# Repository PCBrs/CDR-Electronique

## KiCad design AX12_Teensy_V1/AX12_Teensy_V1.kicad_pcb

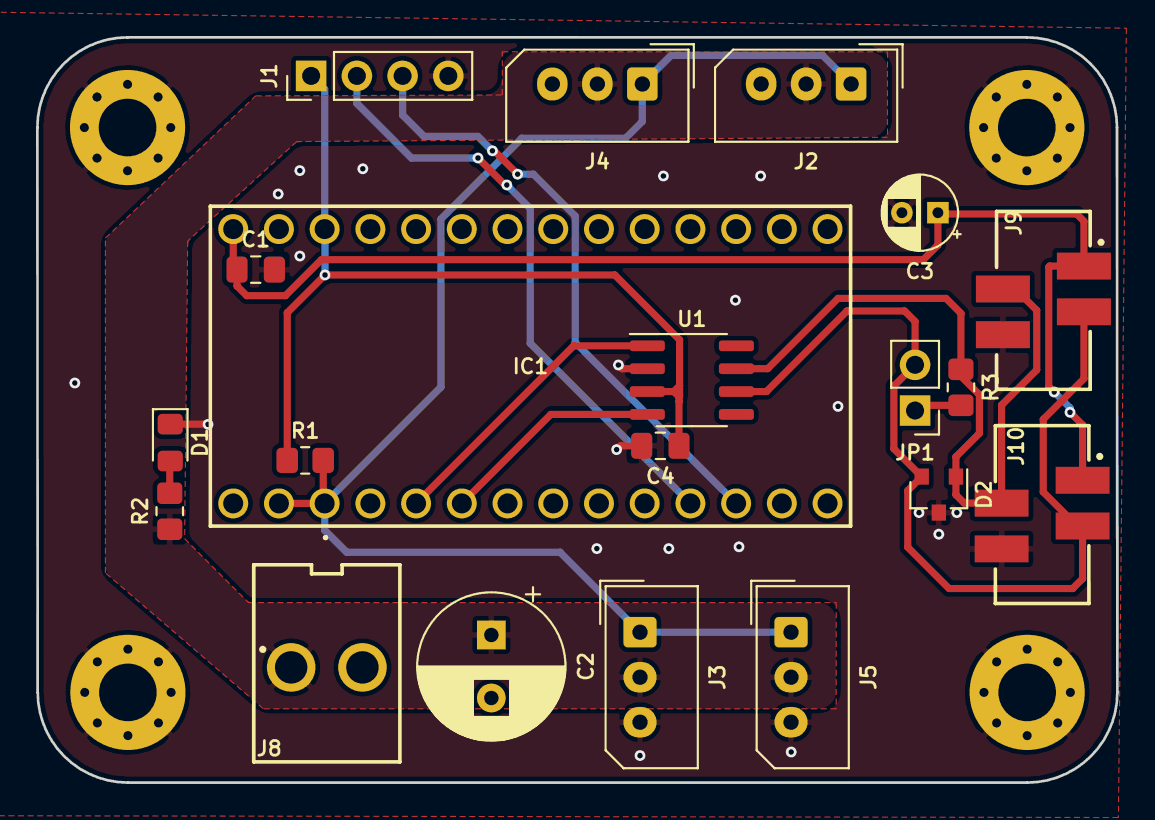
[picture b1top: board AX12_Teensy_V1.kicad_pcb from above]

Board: 2 copper layers, 60.0 x 41.4 mm, 24 parts (0 on the bottom side), 13 nets.

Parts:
C1, C4: 100n; C_0805_2012Metric_Pad1.18x1.45mm_HandSolder
C2: 100u; CP_Radial_D8.0mm_P3.50mm
C3: 10u; CP_Radial_D4.0mm_P2.00mm
D1: LED_12V; LED_0805_2012Metric_Pad1.15x1.40mm_HandSolder
D2: TVS; SOT-23
H1, H2, H3, H4: MountingHole_Pad; MountingHole_3.2mm_M3_Pad_Via
IC1: TEENSY3.2; TEENSY32
J1: uart; PinHeader_1x04_P2.54mm_Vertical
J2, J3, J4, J5: AX12; Molex_SPOX_5267-03A_1x03_P2.50mm_Vertical
J8: 12VP; Wuerth_3.96mm_2pin_645002114822
J9, J10: Conn_CAN; 690367290476
JP1: 120; PinHeader_1x02_P2.54mm_Vertical
R1: 1.5K; R_0805_2012Metric_Pad1.20x1.40mm_HandSolder
R2: 2k; R_0805_2012Metric_Pad1.20x1.40mm_HandSolder
R3: 120; R_0805_2012Metric_Pad1.20x1.40mm_HandSolder
U1: SN65HVD232; SOIC-8_3.9x4.9mm_P1.27mm

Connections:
+3V3: C4.1, IC1.24, J1.1, R1.1, U1.3
+5V: C1.1, C3.1, IC1.26, J9.1, J10.1
+12V: C2.1, J2.2, J3.2, J4.2, J5.2, J8.1, R2.1
/AX12_BUS: IC1.1, IC1.37, J2.1, J3.1, J4.1, J5.1, R1.2
/CANH: D2.1, J9.2, J10.2, R3.1, U1.7
/CANL: D2.2, J9.3, J10.3, JP1.2, U1.6
/CANRX: IC1.4, U1.4
/CANTX: IC1.3, U1.1
/RX: IC1.10, J1.3
/TX: IC1.9, J1.2
GND: C1.2, C2.2, C3.2, C4.2, D1.1, D2.3, H1.1, H2.1, H3.1, H4.1, J1.4, J2.3, J3.3, J4.3, J5.3, J8.2, J9.4, J10.4, U1.2
unnamed: D1.2, R2.2
unnamed: JP1.1, R3.2

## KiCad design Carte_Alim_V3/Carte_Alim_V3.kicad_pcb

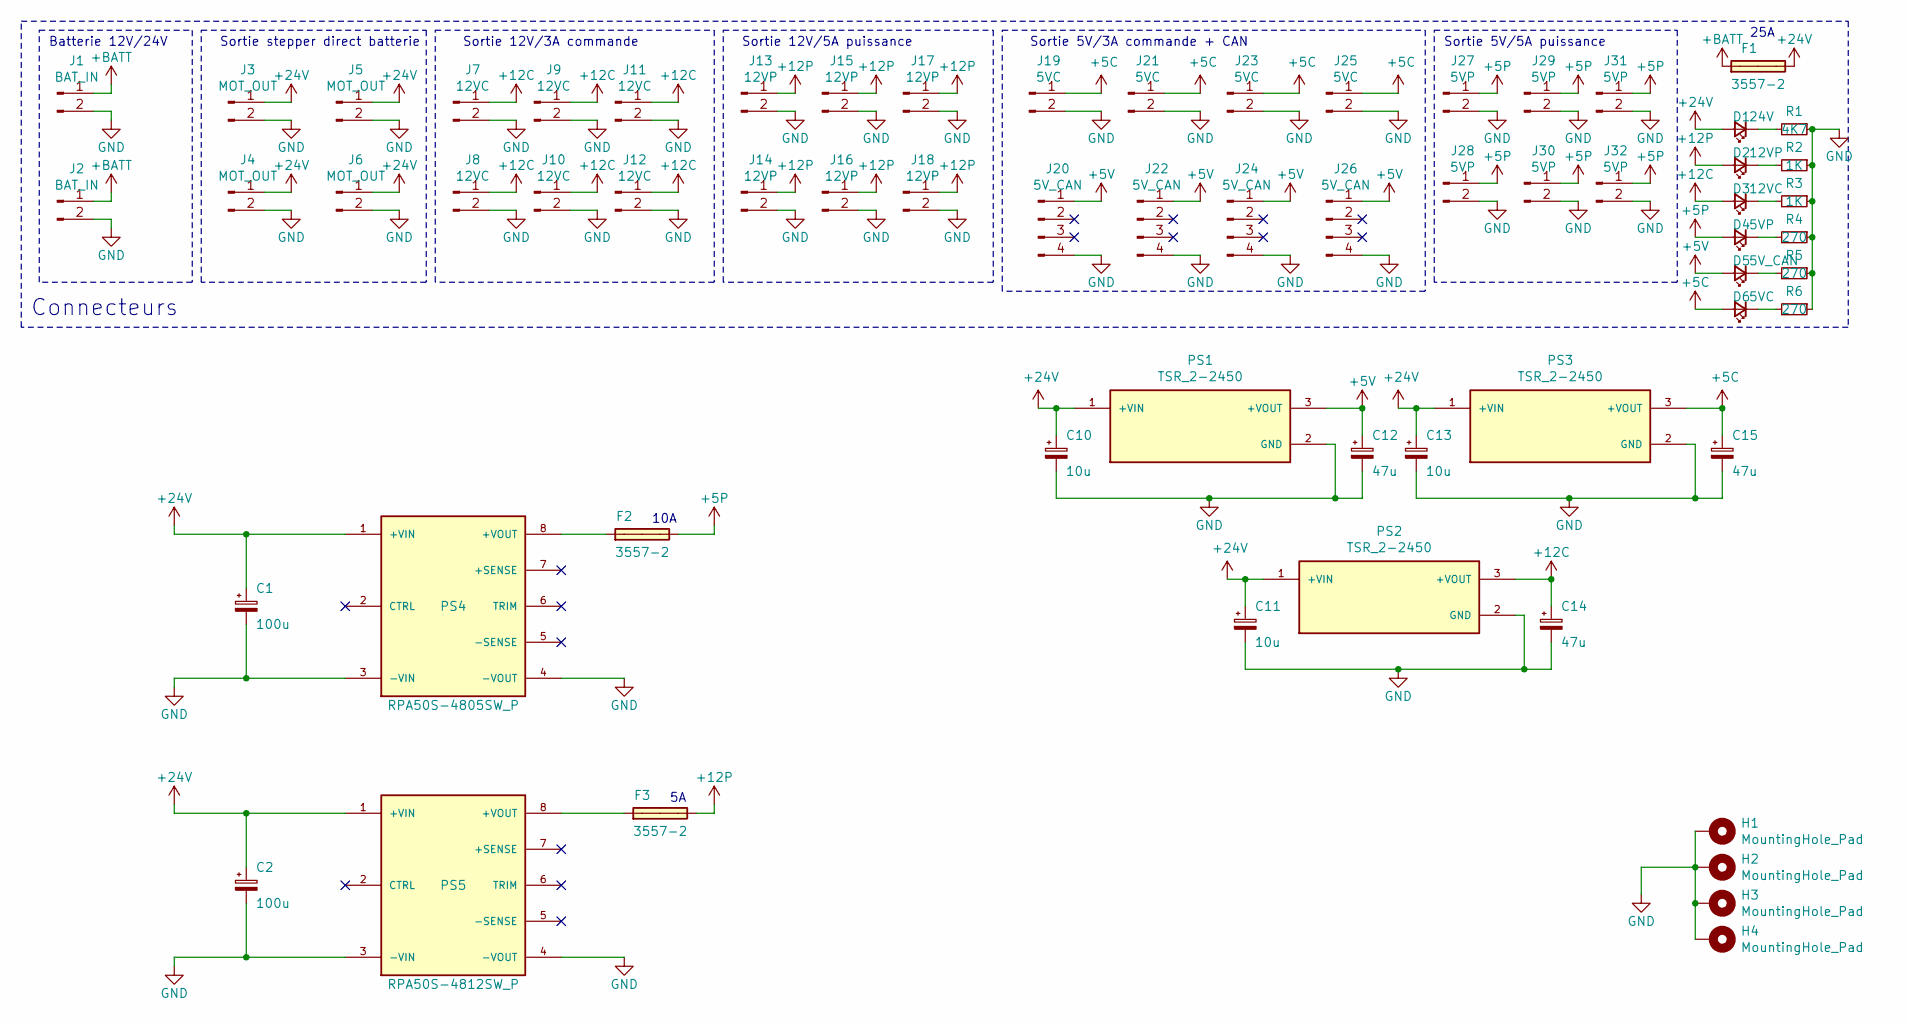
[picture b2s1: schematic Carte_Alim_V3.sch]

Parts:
C1, C2: 100u; CP_Radial_D8.0mm_P3.50mm
C10, C11, C13: 10u; CP_Radial_D4.0mm_P2.00mm
C12, C14, C15: 47u; CP_Radial_D4.0mm_P2.00mm
D1: 24V; LED_0805_2012Metric_Pad1.15x1.40mm_HandSolder
D2: 12VP; LED_0805_2012Metric_Pad1.15x1.40mm_HandSolder
D3: 12VC; LED_0805_2012Metric_Pad1.15x1.40mm_HandSolder
D4: 5VP; LED_0805_2012Metric_Pad1.15x1.40mm_HandSolder
D5: 5V_CAN; LED_0805_2012Metric_Pad1.15x1.40mm_HandSolder
D6: 5VC; LED_0805_2012Metric_Pad1.15x1.40mm_HandSolder
F1, F2, F3: 3557-2; FUSE_3557-2
H1, H2, H3, H4: MountingHole_Pad; MountingHole_3.2mm_M3_Pad_Via
J1, J2: BAT_IN; Wuerth_batcon_691313710002
J3, J4, J5, J6: MOT_OUT; Wuerth_batcon_691313710002
J7, J8, J9, J10, J11, J12: 12VC; Wuerth_2.54mm_2pins_61900211121
J13, J14, J15, J16, J17, J18: 12VP; Wuerth_3.96mm_2pin_645002114822
J19, J21, J23, J25: 5VC; Wuerth_2.54mm_2pins_61900211121
J20, J22, J24, J26: 5V_CAN; Wuerth_2mm_4pin_62000411622
J27, J28, J29, J30, J31, J32: 5VP; Wuerth_3.96mm_2pin_645002114822
PS1, PS2, PS3: TSR_2-2450; CONV_TSR_2-2450; PARTREV May 14, 2020
PS4: RPA50S-4805SW_P; RPA50S-4805SWP; PARTREV 3/2020
PS5: RPA50S-4812SW_P; RPA50S-4812SW; PARTREV 1
R1: 4K7; R_0805_2012Metric_Pad1.20x1.40mm_HandSolder
R2, R3: 1K; R_0805_2012Metric_Pad1.20x1.40mm_HandSolder
R4, R5, R6: 270; R_0805_2012Metric_Pad1.20x1.40mm_HandSolder

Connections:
+5C: C15.1, D6.2 (A), J19.1, J21.1, J23.1, J25.1, PS3.3 (+VOUT)
+5P: D4.2 (A), F2.3, J27.1, J28.1, J29.1, J30.1, J31.1, J32.1
+5V: C12.1, D5.2 (A), J20.1, J22.1, J24.1, J26.1, PS1.3 (+VOUT)
+12C: C14.1, D3.2 (A), J7.1, J8.1, J9.1, J10.1, J11.1, J12.1, PS2.3 (+VOUT)
+12P: D2.2 (A), F3.3, J13.1, J14.1, J15.1, J16.1, J17.1, J18.1
+24V: C1.1, C2.1, C10.1, C11.1, C13.1, D1.2 (A), F1.3, J3.1, J4.1, J5.1, J6.1, PS1.1 (+VIN), PS2.1 (+VIN), PS3.1 (+VIN), PS4.1 (+VIN), PS5.1 (+VIN)
+BATT: F1.1, J1.1, J2.1
GND: C1.2, C2.2, C10.2, C11.2, C12.2, C13.2, C14.2, C15.2, H1.1, H2.1, H3.1, H4.1, J1.2, J2.2, J3.2, J4.2, J5.2, J6.2, J7.2, J8.2, J9.2, J10.2, J11.2, J12.2, J13.2, J14.2, J15.2, J16.2, J17.2, J18.2, J19.2, J20.4, J21.2, J22.4, J23.2, J24.4, J25.2, J26.4, J27.2, J28.2, J29.2, J30.2, J31.2, J32.2, PS1.2 (GND), PS2.2 (GND), PS3.2 (GND), PS4.3 (-VIN), PS4.4 (-VOUT), PS5.3 (-VIN), PS5.4 (-VOUT), R1.1, R2.1, R3.1, R4.1, R5.1, R6.1
unnamed: D1.1 (K), R1.2
unnamed: D2.1 (K), R2.2
unnamed: D3.1 (K), R3.2
unnamed: D4.1 (K), R4.2
unnamed: D5.1 (K), R5.2
unnamed: D6.1 (K), R6.2
unnamed: F2.1, PS4.8 (+VOUT)
unnamed: F3.1, PS5.8 (+VOUT)

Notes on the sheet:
Connecteurs
Batterie 12V/24V
Sortie stepper direct batterie
Sortie 12V/3A commande
Sortie 12V/5A puissance
Sortie 5V/3A commande + CAN
Sortie 5V/5A puissance
10A
25A

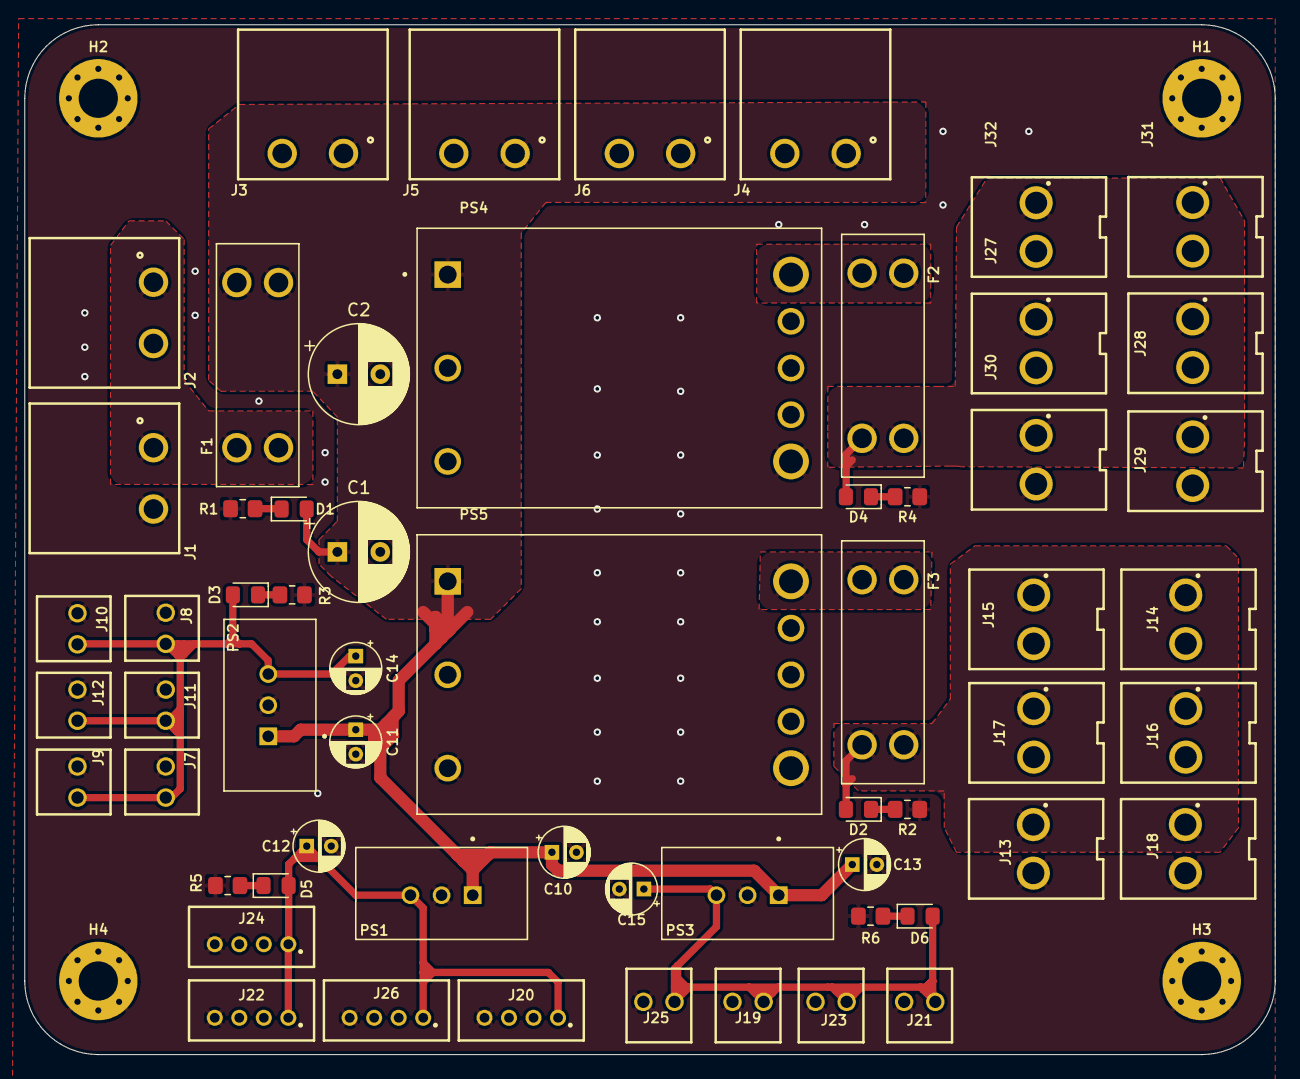
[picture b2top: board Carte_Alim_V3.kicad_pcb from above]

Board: 2 copper layers, 102.0 x 84.0 mm, 64 parts (0 on the bottom side), 16 nets.

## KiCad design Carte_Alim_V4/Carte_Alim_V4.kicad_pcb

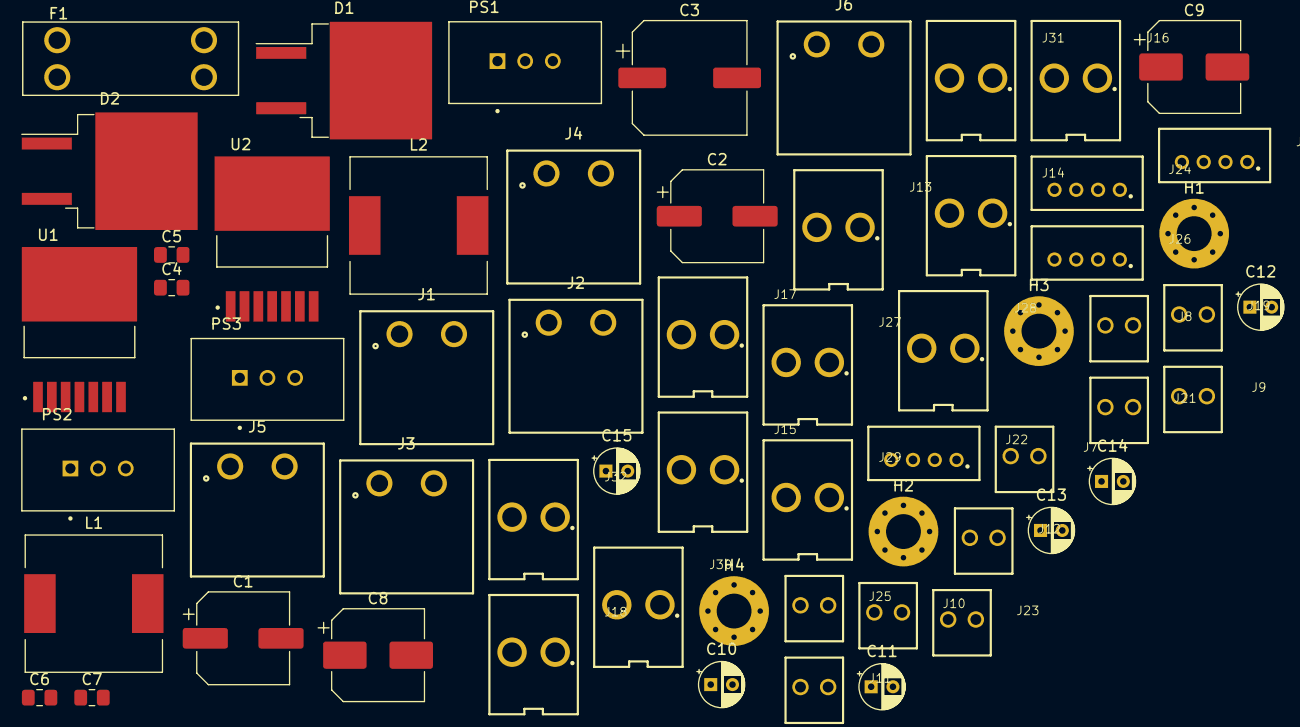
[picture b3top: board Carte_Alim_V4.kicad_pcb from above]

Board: 2 copper layers, 61 parts (0 on the bottom side), 13 nets, no tracks yet.

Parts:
C1, C2: 82u; CP_Elec_8x6.9
C3: 330u; CP_Elec_10x12.6
C4, C5: 100n; C_0805_2012Metric_Pad1.18x1.45mm_HandSolder
C6, C7: 10n; C_0805_2012Metric_Pad1.18x1.45mm_HandSolder
C8, C9: 330u; CP_Elec_8x6.2
C10, C11, C13: 10u; CP_Radial_D4.0mm_P2.00mm
C12, C14, C15: 47u; CP_Radial_D4.0mm_P2.00mm
D1, D2: VB20100S-E3/8W; TO-263-2_TabPin1
F1: 3557-2; FUSE_3557-2
H1, H2, H3, H4: MountingHole_Pad; MountingHole_3.2mm_M3_Pad_Via
J1, J2: BAT_IN; Wuerth_batcon_691313710002
J3, J4, J5, J6: MOT_OUT; Wuerth_batcon_691313710002
J7, J8, J9, J10, J11, J12: 12VC; Wuerth_2.54mm_2pins_61900211121
J13, J14, J15, J16, J17, J18: 12VP; Wuerth_3.96mm_2pin_645002114822
J19, J21, J23, J25: 5VC; Wuerth_2.54mm_2pins_61900211121
J20, J22, J24, J26: 5V_CAN; Wuerth_2mm_4pin_62000411622
J27, J28, J29, J30, J31, J32: 5VP; Wuerth_3.96mm_2pin_645002114822
L1, L2: MSS1210-153MED; L_12x12mm_H8mm
PS1, PS2, PS3: TSR_2-2450; CONV_TSR_2-2450
U1: LM2678S-5.0; TO127P1435X464-8N
U2: LM2678S-12; TO127P1435X464-8N

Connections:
+5C: C15.1, J19.1, J21.1, J23.1, J25.1, PS3.3
+5P: C8.1, J27.1, J28.1, J29.1, J30.1, J31.1, J32.1, L1.2, U1.6
+5V: C12.1, J20.1, J22.1, J24.1, J26.1, PS1.3
+12C: C14.1, J7.1, J8.1, J9.1, J10.1, J11.1, J12.1, PS2.3
+12P: C9.1, J13.1, J14.1, J15.1, J16.1, J17.1, J18.1, L2.2, U2.6
+24V: C1.1, C2.1, C3.1, C4.1, C5.1, C10.1, C11.1, C13.1, F1.3, PS1.1, PS2.1, PS3.1, U1.2, U2.2
+BATT: F1.1, J1.1, J2.1, J3.1, J4.1, J5.1, J6.1
GND: C1.2, C2.2, C4.2, C8.2, C10.2, C11.2, C12.2, C13.2, C14.2, C15.2, D1.2, H1.1, H2.1, H3.1, H4.1, J1.2, J2.2, J3.2, J4.2, J5.2, J6.2, J7.2, J8.2, J9.2, J10.2, J11.2, J12.2, J13.2, J14.2, J15.2, J16.2, J17.2, J18.2, J19.2, J20.4, J21.2, J22.4, J23.2, J24.4, J25.2, J26.4, J27.2, J28.2, J29.2, J30.2, J31.2, J32.2, PS1.2, PS2.2, PS3.2, U1.4, U1.8
unnamed: C3.2, C5.2, C9.2, D2.2, U2.4, U2.8
unnamed: C6.1, U1.3
unnamed: C6.2, D1.1, L1.1, U1.1
unnamed: C7.1, U2.3
unnamed: C7.2, D2.1, L2.1, U2.1

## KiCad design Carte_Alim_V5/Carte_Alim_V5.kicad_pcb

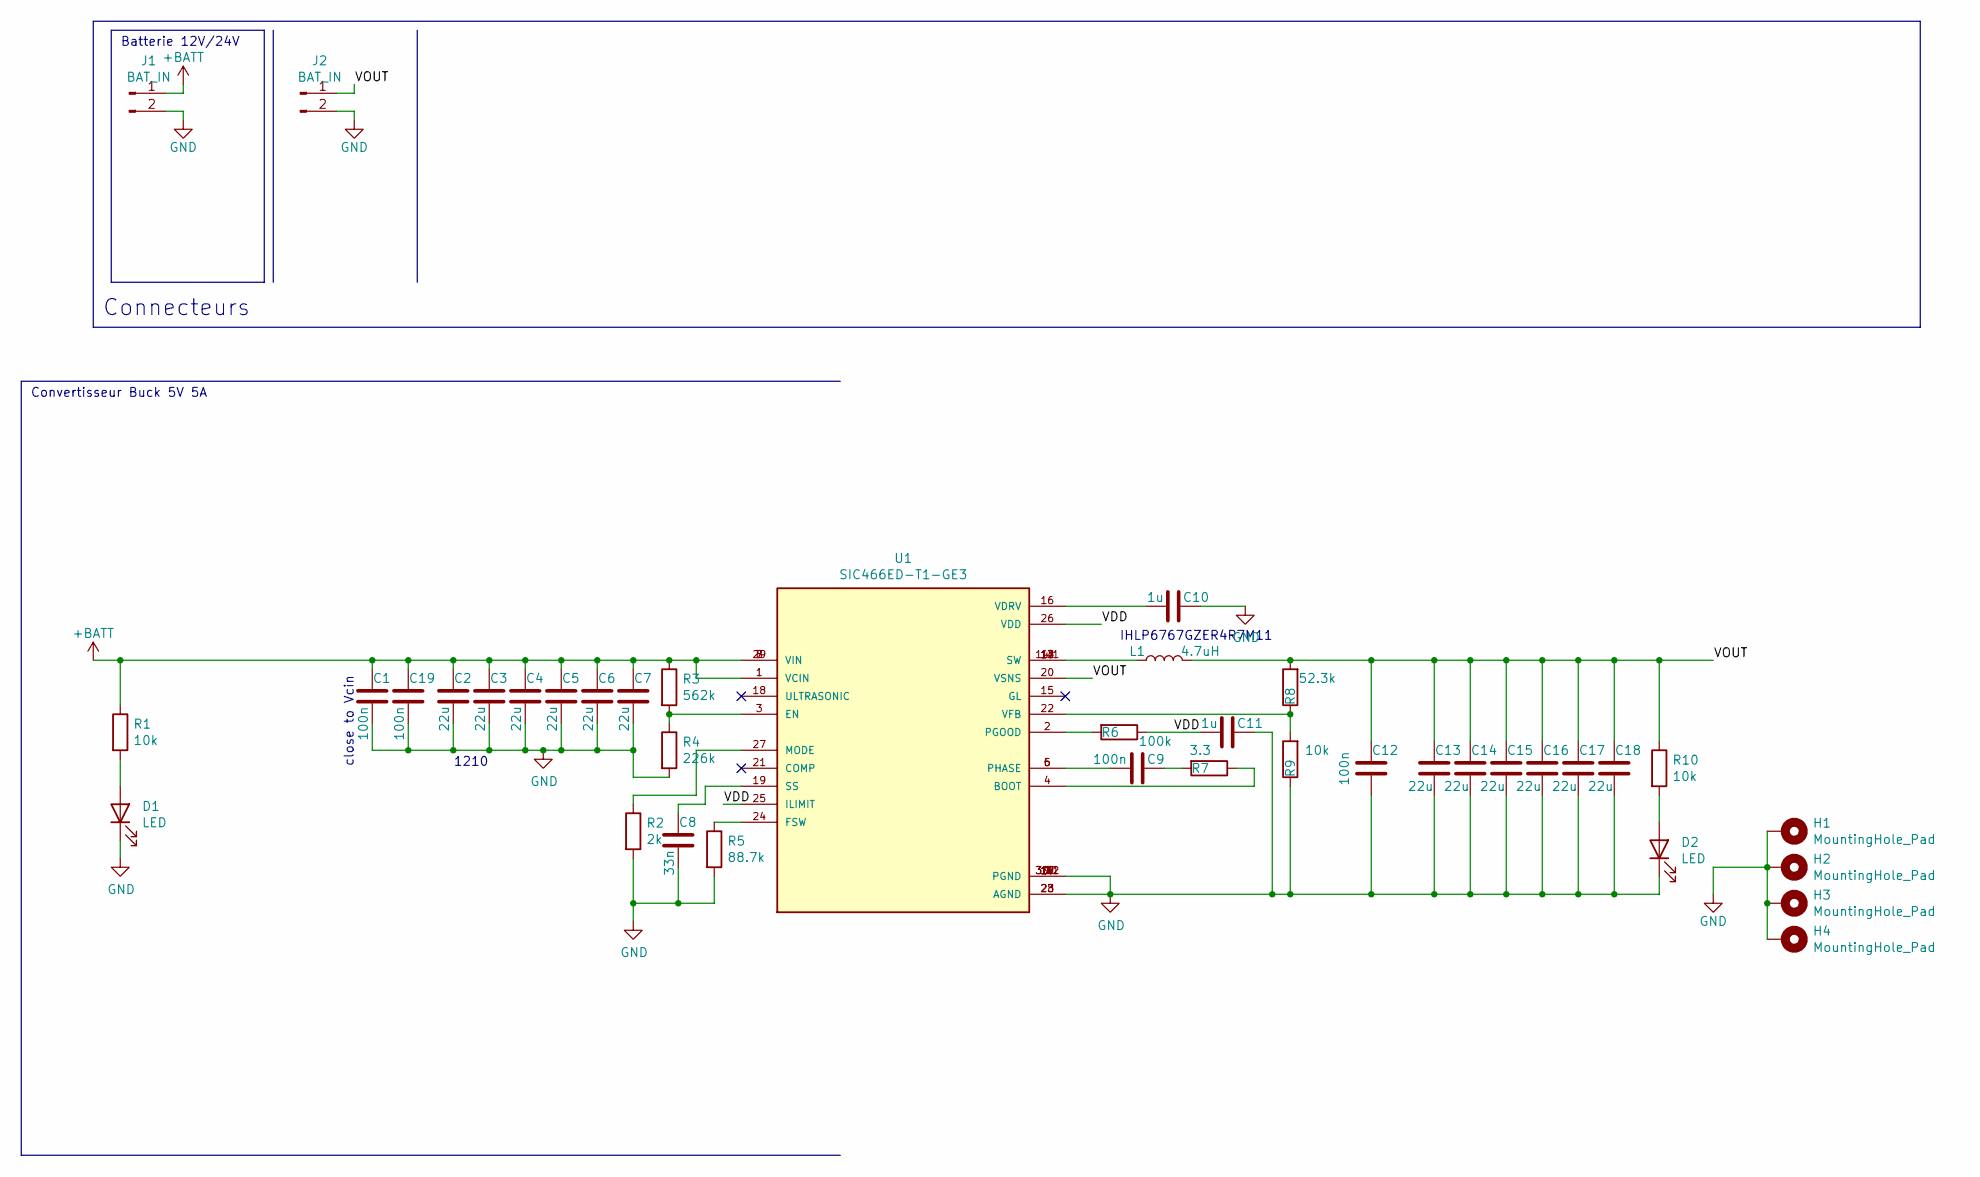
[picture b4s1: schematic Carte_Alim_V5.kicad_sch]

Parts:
C1, C9, C12, C19: 100n; C_0805_2012Metric_Pad1.15x1.40mm_HandSolder
C2, C3, C4, C5, C6, C7, C13, C14, C15, C16, C17, C18: 22u; C_1210_3225Metric_Pad1.42x2.65mm_HandSolder
C8: 33n; C_0805_2012Metric_Pad1.15x1.40mm_HandSolder
C10, C11: 1u; C_0805_2012Metric_Pad1.15x1.40mm_HandSolder
D1, D2: LED; LED_0805_2012Metric_Pad1.15x1.40mm_HandSolder
H1, H2, H3, H4: MountingHole_Pad; MountingHole_3.2mm_M3_Pad_Via
J1, J2: BAT_IN; PhoenixContact_MSTBVA_2,5_2-G-5,08_1x02_P5.08mm_Vertical
L1: 4.7uH; L_Vishay_IHLP-6767
R1, R9: 10k; R_0603_1608Metric_Pad1.05x0.95mm_HandSolder
R2: 2k; R_0603_1608Metric_Pad1.05x0.95mm_HandSolder
R3: 562k; R_0603_1608Metric_Pad1.05x0.95mm_HandSolder
R4: 226k; R_0603_1608Metric_Pad1.05x0.95mm_HandSolder
R5: 88.7k; R_0603_1608Metric_Pad1.05x0.95mm_HandSolder
R6: 100k; R_0603_1608Metric_Pad1.05x0.95mm_HandSolder
R7: 3.3; R_0603_1608Metric_Pad1.05x0.95mm_HandSolder
R8: 52.3k; R_0603_1608Metric_Pad1.05x0.95mm_HandSolder
R10: 10k; R_0603_1608Metric_Pad0.98x0.95mm_HandSolder
U1: SIC466ED-T1-GE3; CONV_SIC461ED-T1-GE3; PARTREV M

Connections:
+BATT: C1.1, C2.1, C3.1, C4.1, C5.1, C6.1, C7.1, C19.1, J1.1, R1.1, R3.1, U1.1 (VCIN), U1.7 (VIN), U1.8 (VIN), U1.29 (VIN)
/VDD: C11.2, R6.1, U1.25 (ILIMIT), U1.26 (VDD)
/VOUT: C12.1, C13.1, C14.1, C15.1, C16.1, C17.1, C18.1, J2.1, L1.2, R8.2, R10.1, U1.20 (VSNS)
GND: C1.2, C2.2, C3.2, C4.2, C5.2, C6.2, C7.2, C8.2, C10.1, C11.1, C12.2, C13.2, C14.2, C15.2, C16.2, C17.2, C18.2, C19.2, D1.1 (K), D2.1 (K), H1.1, H2.1, H3.1, H4.1, J1.2, J2.2, R2.2, R4.2, R5.2, R9.1, U1.9 (PGND), U1.10 (PGND), U1.11 (PGND), U1.17 (PGND), U1.23 (AGND), U1.28 (AGND), U1.30.1 (PGND), U1.30.2 (PGND)
unnamed: C8.1, U1.19 (SS)
unnamed: C9.1, R7.2
unnamed: C9.2, U1.5 (PHASE), U1.6 (PHASE)
unnamed: C10.2, U1.16 (VDRV)
unnamed: D1.2 (A), R1.2
unnamed: D2.2 (A), R10.2
unnamed: L1.1, U1.12 (SW), U1.13 (SW), U1.14 (SW), U1.14.1 (SW)
unnamed: R2.1, U1.27 (MODE)
unnamed: R3.2, R4.1, U1.3 (EN)
unnamed: R5.1, U1.24 (FSW)
unnamed: R6.2, U1.2 (PGOOD)
unnamed: R7.1, U1.4 (BOOT)
unnamed: R8.1, R9.2, U1.22 (VFB)

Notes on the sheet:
Convertisseur Buck 5V 5A
1210
close to Vcin
Connecteurs
IHLP6767GZER4R7M11
Batterie 12V/24V

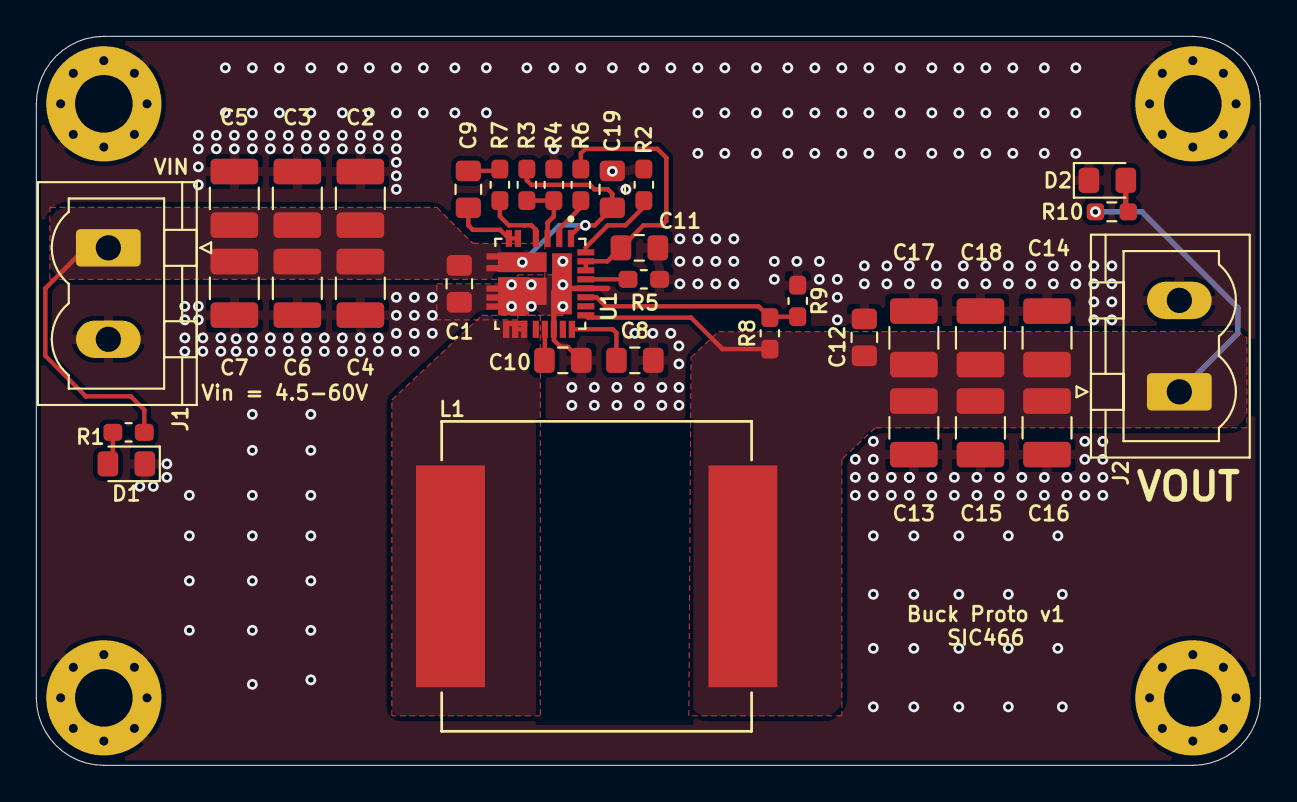
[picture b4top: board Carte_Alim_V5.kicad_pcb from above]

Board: 2 copper layers, 68.0 x 40.5 mm, 39 parts (0 on the bottom side), 17 nets.

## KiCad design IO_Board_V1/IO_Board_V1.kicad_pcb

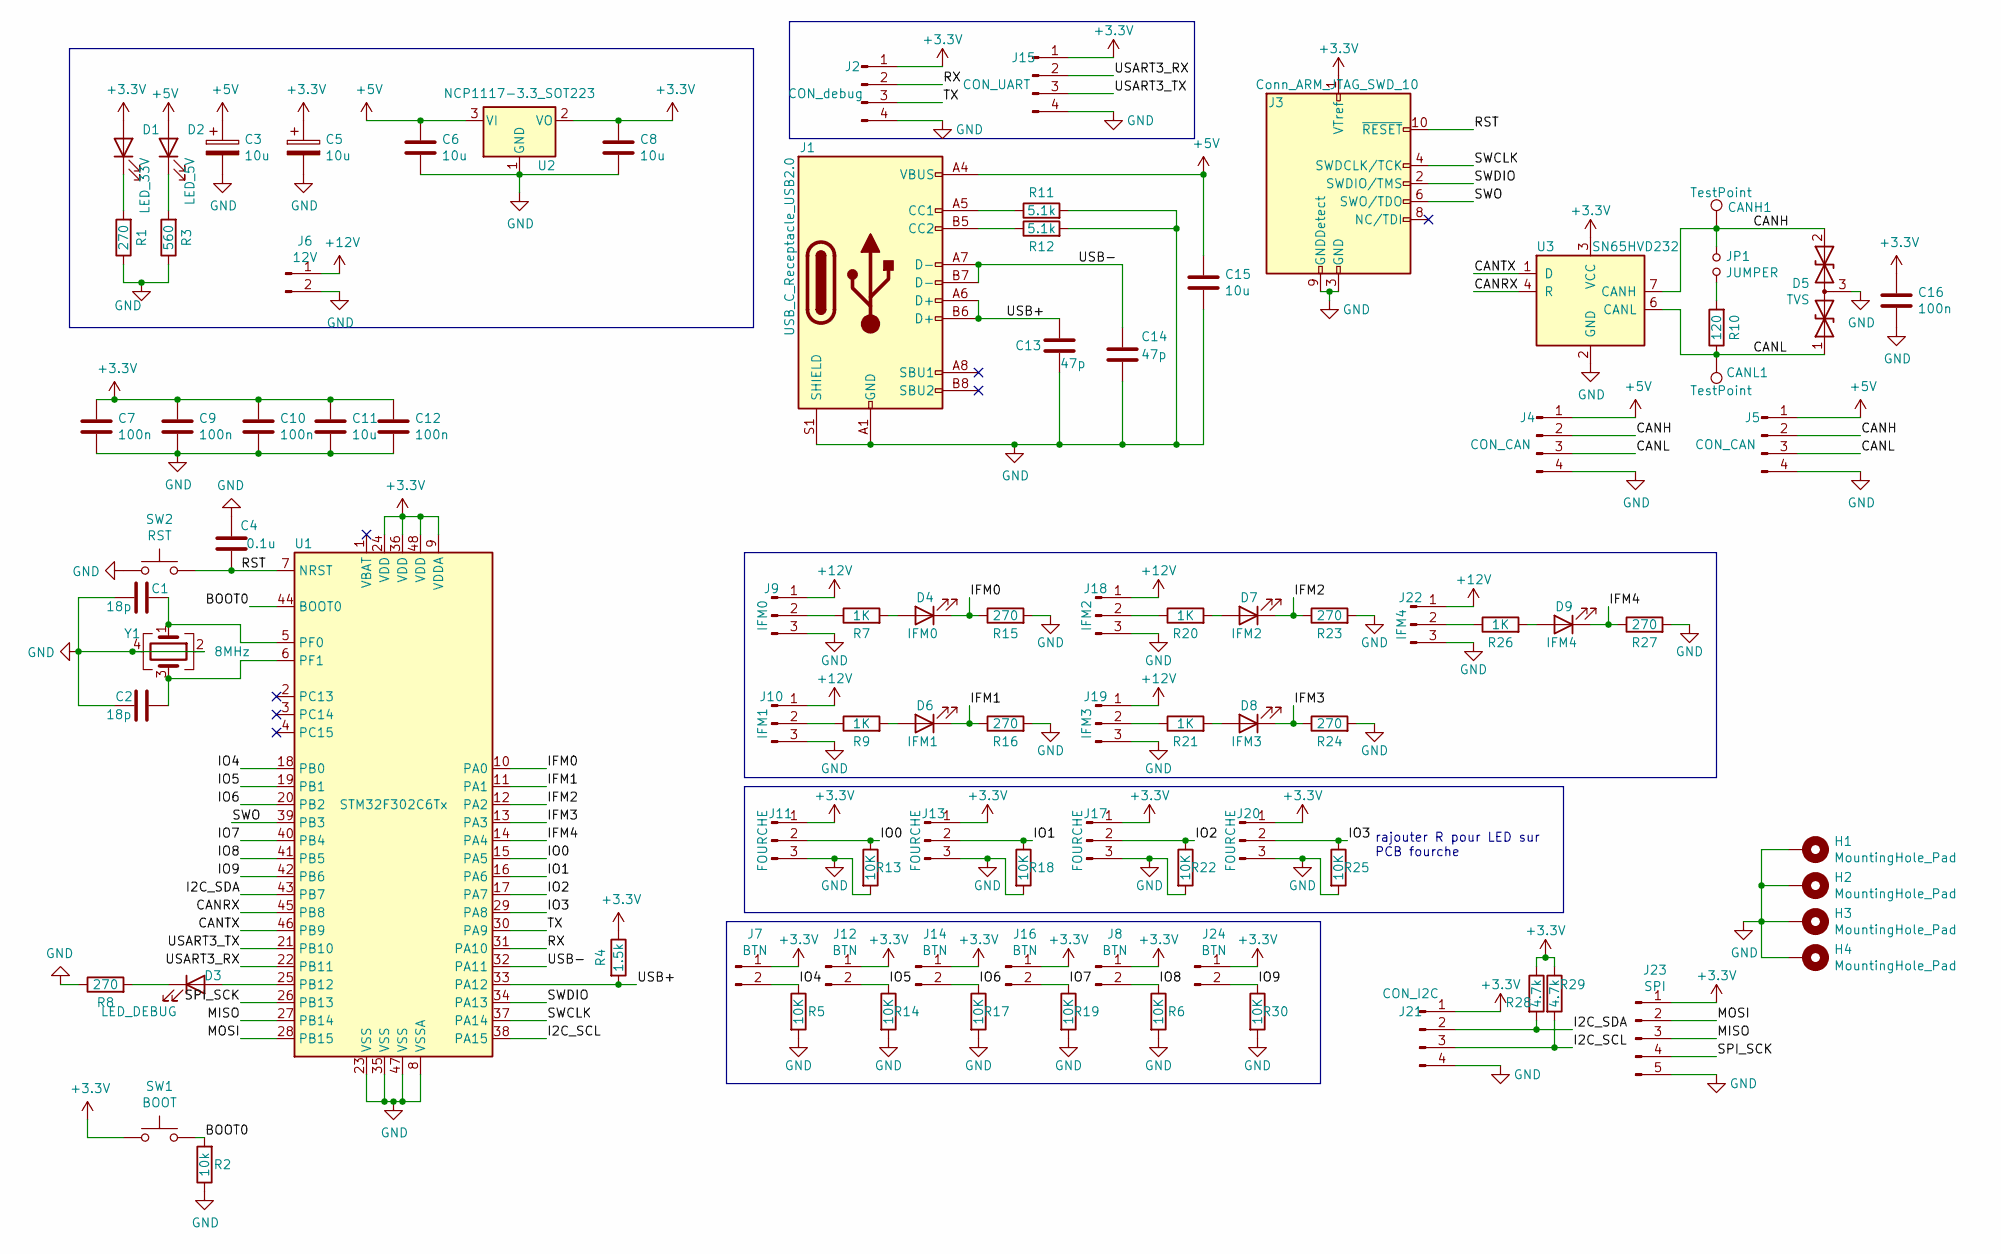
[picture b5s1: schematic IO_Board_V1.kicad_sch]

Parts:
C1, C2: 18p; C_0805_2012Metric_Pad1.18x1.45mm_HandSolder
C3, C5: 10u; CP_Radial_D4.0mm_P2.00mm
C4: 0.1u; C_0805_2012Metric
C6, C8, C11, C15: 10u; C_0805_2012Metric
C7, C9, C10, C12, C16: 100n; C_0805_2012Metric
C13, C14: 47p; C_0805_2012Metric
CANH1: TestPoint; TestPoint_Loop_D1.80mm_Drill1.0mm_Beaded
CANL1: TestPoint; TestPoint_Loop_D1.80mm_Drill1.0mm_Beaded
D1: LED_33V; LED_0805_2012Metric
D2: LED_5V; LED_0805_2012Metric
D3: LED_DEBUG; LED_0805_2012Metric
D4: IFM0; LED_0805_2012Metric
D5: TVS; SOT-23
D6: IFM1; LED_0805_2012Metric
D7: IFM2; LED_0805_2012Metric
D8: IFM3; LED_0805_2012Metric
D9: IFM4; LED_0805_2012Metric
H1, H2, H3, H4: MountingHole_Pad; MountingHole_3.2mm_M3_Pad_Via
J1: USB_C_Receptacle_USB2.0; USB_C_Receptacle_GCT_USB4085
J2: CON_debug; Wuerth_2.54mm_4pins_61900411121
J3: Conn_ARM_JTAG_SWD_10; PinHeader_2x05_P1.27mm_Vertical
J4, J5: CON_CAN; 690367290476
J6: 12V; Wuerth_2.54mm_2pins_61900211121
J7, J8, J12, J14, J16, J24: BTN; Wuerth_2.54mm_2pins_61900211121
J9: IFM0; Wuerth_2.54mm_3pins_61900311121
J10: IFM1; Wuerth_2.54mm_3pins_61900311121
J11, J13, J17, J20: FOURCHE; Wuerth_2.54mm_3pins_61900311121
J15: CON_UART; Wuerth_2.54mm_4pins_61900411121
J18: IFM2; Wuerth_2.54mm_3pins_61900311121
J19: IFM3; Wuerth_2.54mm_3pins_61900311121
J21: CON_I2C; Wuerth_2.54mm_4pins_61900411121
J22: IFM4; Wuerth_2.54mm_3pins_61900311121
J23: SPI; Wuerth_2.54mm_5pins_61900511121
JP1: JUMPER; PinHeader_1x02_P2.54mm_Vertical
R1, R8, R15, R16, R23, R24, R27: 270; R_0805_2012Metric
R2: 10k; R_0805_2012Metric
R3: 560; R_0805_2012Metric
R4: 1.5k; R_0805_2012Metric
R5, R6, R13, R14, R17, R18, R19, R22, R25, R30: 10K; R_0805_2012Metric
R7, R9, R20, R21, R26: 1K; R_0805_2012Metric
R10: 120; R_0805_2012Metric
R11, R12: 5.1k; R_0805_2012Metric
R28, R29: 4.7k; R_0805_2012Metric
SW1: BOOT; SW_SPST_CK_RS282G05A3
SW2: RST; SW_SPST_CK_RS282G05A3
U1: STM32F302C6Tx; LQFP-48_7x7mm_P0.5mm
U2: NCP1117-3.3_SOT223; SOT-223-3_TabPin2
U3: SN65HVD232; SOIC-8_3.9x4.9mm_P1.27mm
Y1: 8MHz; Crystal_SMD_5032-4Pin_5.0x3.2mm

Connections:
+3V3: C5.1, C7.1, C8.1, C9.1, C10.1, C11.1, C12.1, C16.1, D1.2 (A), J2.1, J3.1 (VTref), J7.1, J8.1, J11.1, J12.1, J13.1, J14.1, J15.1, J16.1, J17.1, J20.1, J21.1, J23.1, J24.1, R4.1, R28.1, R29.1, SW1.1, U1.9 (VDDA), U1.24 (VDD), U1.36 (VDD), U1.48 (VDD), U2.2 (VO), U3.3 (VCC)
+5V: C3.1, C6.1, C15.1, D2.2 (A), J1.A4 (VBUS), J1.A9 (VBUS), J1.B4 (VBUS), J1.B9 (VBUS), J4.1, J5.1, U2.3 (VI)
+12V: J6.1, J9.1, J10.1, J18.1, J19.1, J22.1
/BOOT0: R2.2, SW1.2, U1.44 (BOOT0)
/CANH: CANH1.1, D5.2 (A2), J4.2, J5.2, JP1.1, U3.7 (CANH)
/CANL: CANL1.1, D5.1 (A1), J4.3, J5.3, R10.1, U3.6 (CANL)
/CANRX: U1.45 (PB8), U3.4 (R)
/CANTX: U1.46 (PB9), U3.1 (D)
/I2C_SCL: J21.3, R29.2, U1.38 (PA15)
/I2C_SDA: J21.2, R28.2, U1.43 (PB7)
/IFM0: D4.1 (K), R15.1, U1.10 (PA0)
/IFM1: D6.1 (K), R16.1, U1.11 (PA1)
/IFM2: D7.1 (K), R23.1, U1.12 (PA2)
/IFM3: D8.1 (K), R24.1, U1.13 (PA3)
/IFM4: D9.1 (K), R27.1, U1.14 (PA4)
/IO0: J11.2, R13.1, U1.15 (PA5)
/IO1: J13.2, R18.1, U1.16 (PA6)
/IO2: J17.2, R22.1, U1.17 (PA7)
/IO3: J20.2, R25.1, U1.29 (PA8)
/IO4: J7.2, R5.1, U1.18 (PB0)
/IO5: J12.2, R14.1, U1.19 (PB1)
/IO6: J14.2, R17.1, U1.20 (PB2)
/IO7: J16.2, R19.1, U1.40 (PB4)
/IO8: J8.2, R6.1, U1.41 (PB5)
/IO9: J24.2, R30.1, U1.42 (PB6)
/MISO: J23.3, U1.27 (PB14)
/MOSI: J23.2, U1.28 (PB15)
/RST: C4.1, J3.10 (~RESET), SW2.2, U1.7 (NRST)
/RX: J2.2, U1.31 (PA10)
/SPI_SCK: J23.4, U1.26 (PB13)
/SWCLK: J3.4 (SWDCLK/TCK), U1.37 (PA14)
/SWDIO: J3.2 (SWDIO/TMS), U1.34 (PA13)
/SWO: J3.6 (SWO/TDO), U1.39 (PB3)
/TX: J2.3, U1.30 (PA9)
/USART3_RX: J15.2, U1.22 (PB11)
/USART3_TX: J15.3, U1.21 (PB10)
/USB+: C13.1, J1.A6 (D+), J1.B6 (D+), R4.2, U1.33 (PA12)
/USB-: C14.1, J1.A7 (D-), J1.B7 (D-), U1.32 (PA11)
GND: C1.2, C2.2, C3.2, C4.2, C5.2, C6.2, C7.2, C8.2, C9.2, C10.2, C11.2, C12.2, C13.2, C14.2, C15.2, C16.2, D5.3 (common), H1.1, H2.1, H3.1, H4.1, J1.A1 (GND), J1.A12 (GND), J1.B1 (GND), J1.B12 (GND), J1.S1 (SHIELD), J2.4, J3.3 (GND), J3.5 (GND), J3.9 (GNDDetect), J4.4, J5.4, J6.2, J9.3, J10.3, J11.3, J13.3, J15.4, J17.3, J18.3, J19.3, J20.3, J21.4, J22.3, J23.5, R1.1, R2.1, R3.1, R5.2, R6.2, R8.1, R11.2, R12.2, R13.2, R14.2, R15.2, R16.2, R17.2, R18.2, R19.2, R22.2, R23.2, R24.2, R25.2, R27.2, R30.2, SW2.1, U1.8 (VSSA), U1.23 (VSS), U1.35 (VSS), U1.47 (VSS), U2.1 (GND), U3.2 (GND), Y1.2, Y1.4
unnamed: C1.1, U1.5 (PF0), Y1.1
unnamed: C2.1, U1.6 (PF1), Y1.3
unnamed: D1.1 (K), R1.2
unnamed: D2.1 (K), R3.2
unnamed: D3.1 (K), R8.2
unnamed: D3.2 (A), U1.25 (PB12)
unnamed: D4.2 (A), R7.2
unnamed: D6.2 (A), R9.2
unnamed: D7.2 (A), R20.2
unnamed: D8.2 (A), R21.2
unnamed: D9.2 (A), R26.2
unnamed: J1.A5 (CC1), R11.1
unnamed: J1.B5 (CC2), R12.1
unnamed: J9.2, R7.1
unnamed: J10.2, R9.1
unnamed: J18.2, R20.1
unnamed: J19.2, R21.1
unnamed: J22.2, R26.1
unnamed: JP1.2, R10.2

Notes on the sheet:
rajouter R pour LED sur PCB fourche

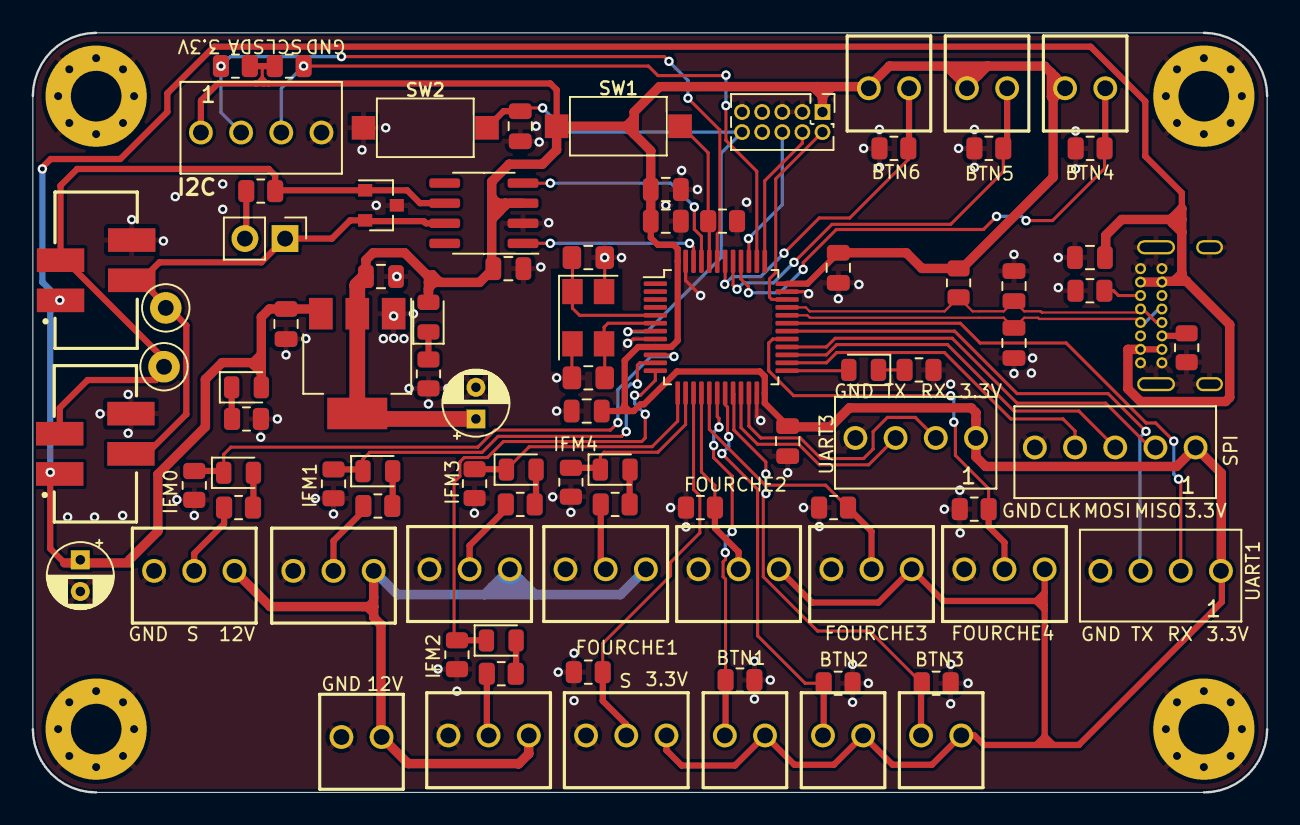
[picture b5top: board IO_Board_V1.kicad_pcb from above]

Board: 2 copper layers, 78.0 x 48.0 mm, 92 parts (1 on the bottom side), 58 nets.
